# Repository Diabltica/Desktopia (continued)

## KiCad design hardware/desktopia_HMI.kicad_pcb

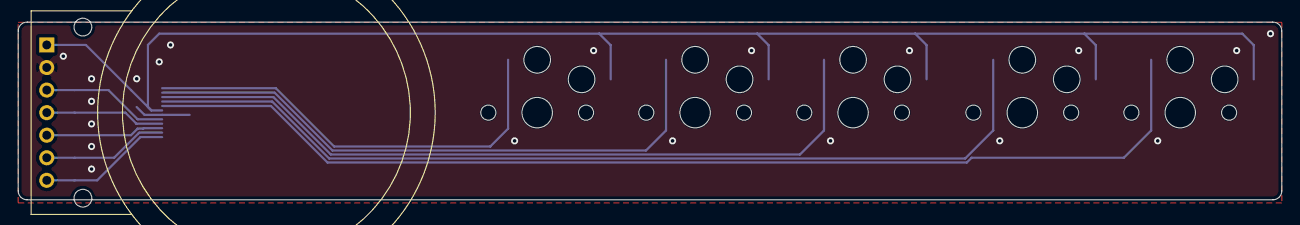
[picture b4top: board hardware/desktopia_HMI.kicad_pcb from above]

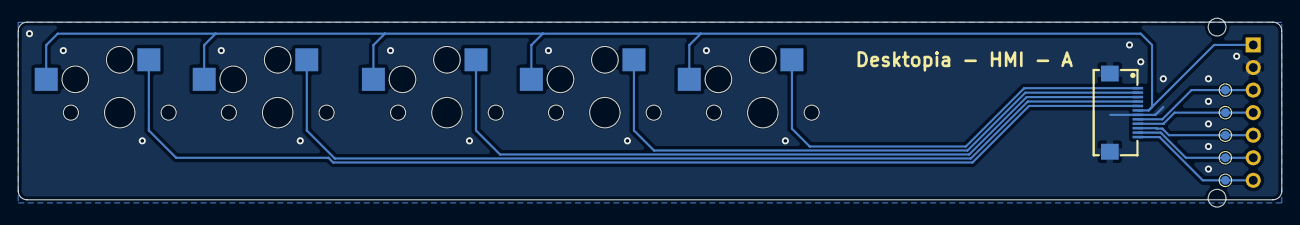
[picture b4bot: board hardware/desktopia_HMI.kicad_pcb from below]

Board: 2 copper layers, 142.2 x 21.3 mm, 12 parts (6 on the bottom side), 12 nets.

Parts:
FPC_HMI1: F2D12U-A1G1-ER
J1: LCD_Connector; LCD_round_screen
SW1, SW2, SW3, SW4, SW5: SW_Push; PG1350
TP2, TP3, TP4, TP5, TP6: TestPoint; TestPoint_Pad_D1.0mm

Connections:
+5VA: FPC_HMI1.6, J1.1, SW1.2, SW2.2, SW3.2, SW4.2, SW5.2
/CS_HMIside: FPC_HMI1.11, J1.6, TP5.1 (1_1)
/DC_HMIside: FPC_HMI1.10, J1.5, TP4.1 (1_1)
/MOSI_HMIside: FPC_HMI1.9, J1.4, TP3.1 (1_1)
/RST_HMIside: FPC_HMI1.12, J1.7, TP6.1 (1_1)
/SCK_HMIside: FPC_HMI1.8, J1.3, TP2.1 (1_1)
/SW1_HMIside: FPC_HMI1.1, SW1.1
/SW2_HMIside: FPC_HMI1.2, SW2.1
/SW3_HMIside: FPC_HMI1.3, SW3.1
/SW4_HMIside: FPC_HMI1.4, SW4.1
/SW5_HMIside: FPC_HMI1.5, SW5.1
GNDA: FPC_HMI1.7, FPC_HMI1.13, FPC_HMI1.14, J1.2

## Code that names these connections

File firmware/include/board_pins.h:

#pragma once
/*
 * Desktopia motherboard – pin map extracted from desktopia.kicad_sch (RJ11 / RS-485 HMI version)
 * ---------------------------------------------------------------------------
 * MCU: ATmega32U4 (TQFP-44), 16 MHz crystal, +5 V.
 * Numbers below are Arduino pin numbers of the PlatformIO "leonardo" variant.
 * (port / TQFP pin / schematic net in the comments)
 */
#include <Arduino.h>

namespace pins {

// --- Motor command, connector J6 "MotorCommandCon" (1 = Mdir, 2 = Mpwm, 3 = GND), 10k pull-downs
constexpr uint8_t MOTOR_DIR = 5;    // PC6  – TQFP 31 – net Mdir
constexpr uint8_t MOTOR_PWM = 10;   // PB6  – TQFP 30 – net Mpwm – OC1B (Timer1 hardware PWM)

// --- Motor driver supply: HIGH = Q5 (P-MOSFET high-side switch) feeds J5. Pull-down R22: off during a reset.
constexpr uint8_t MOTOR_POWER = 6;  // PD7  – TQFP 27 – net MOTOR_PWR
constexpr uint8_t MOTOR_POWER_PORT_BIT = 7;   // PORTD bit, for the register-only cut in interrupts

// --- INA226 alert: open drain, active low, 4.7k pull-up R25, 100 pF filter C23
constexpr uint8_t I_ALERT = 7;      // PE6  – TQFP 1  – net I_ALERT – INT6

// --- HMI board link: RS-485 transceiver U5 (SP485EEN), RJ11 jack J4
//   RX = PD2 (D0) – TQFP 20 – U5 RO            TX = PD3 (D1) – TQFP 21 – U5 DI          → Serial1
constexpr uint8_t RS485_DE = 4;     // PD4  – TQFP 25 – U5 DE and /RE, tied: HIGH = drive the bus

// --- I2C bus: VL53L1CB ToF (0x29) behind the BSS138 level shifters Q1 / Q2 (2.8 V side),
//     INA226 motor current monitor U6 (0x40) on the 5 V side
//   SDA = PD1 (D2), SCL = PD0 (D3): hardware TWI via Wire

// --- Not used by this firmware
//   PB4 (D8) = TOF_INT: VL53L1CB GPIO1 (data ready) through level shifter Q3, 10k pull-up R10 (PCINT4)
//   PF0 (A5) is now free (it read the old analog current sensor)
//   PB1 / PB2 / PB3 (SCK / MOSI / MISO) only go to the ISP header J2

}  // namespace pins

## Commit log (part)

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2023-09-25 add readme and some documentation
2023-09-25 change readme extension
2023-09-25 update architecture
2023-09-25 create kicad project
